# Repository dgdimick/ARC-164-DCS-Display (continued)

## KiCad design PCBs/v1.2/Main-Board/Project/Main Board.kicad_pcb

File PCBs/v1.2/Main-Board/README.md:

# ARC-164 Main Board — Version 1.2

**Last updated: November 10, 2026 at 6:08 PM MST (America/Denver)**

**LED Sub Board v1.2 is now published for Main Board v1.2.** I printed the latest mockup at **100%** and it passed the fit test, including **frequency and channel LED alignment and J20 connector/cable clearance**. The final layout keeps the **FREQ LEDs up 0.5 mm**, the **channel LEDs up 0.5 mm with their earlier 0.5 mm leftward adjustment**, and **J20 up 2 mm total** from the previous mounting position. The **0.75 mm gaps, 6 mm display bodies and tested 8 mm mounting stack** remain unchanged. **Use Main Board v1.2 with LED Sub Board v1.2; older Sub Boards do not match this Main Board. Assembled electrical testing is still pending.**

## Downloads

- [Complete Main Board v1.2 package](Main-Board-v1.2.zip)
- [KiCad project](Project/Main%20Board.kicad_pro)
- [Schematic PDF](Schematics/Main-Board-v1.2.pdf)
- [Component BOM](Assembly/BOM.csv)
- [Gerber and drill ZIP](Main-Board-v1.2-Gerbers.zip)
- [Main Board print mockup — 100% scale](STLs/ARC-164_Main_Board_v1.2_100pct.stl)
- [DRC and schematic parity report](Checks/DRC.rpt) · [ERC report](Checks/ERC.rpt)

I’ve resized this Main Board and moved the Sub Board mounting holes to match the new layout. The silkscreen and PCB/schematic revision fields identify **v1.2**. This release contains only the Main Board; it does not include the unfinished matching Sub Board.

I moved **J10 to my chosen position**, aligned **SW12 (LOAD/reed) and SW13 (TEST DISPLAY)** below R4, and updated the routing and ground fills. Their matching solder pads now line up horizontally. All other component positions, the outline and mounting holes are unchanged from my latest saved layout.

Fresh KiCad checks report **zero DRC violations, zero unconnected items, zero schematic parity issues and zero ERC violations under the saved project settings**. Disabled checks are listed in the reports. These checks do not prove physical cable clearance or assembled electrical operation. The two 40-pin interfaces use cables, not direct stacking connectors.

## Mounting and compatibility

**Use Main Board v1.2 with the matching LED Sub Board v1.2.** The latest Sub Board mockup passed my **100% print and fit test on November 10, 2026**, including LED alignment and J20 connector/cable clearance. Older Sub Boards do not match Main Board v1.2. Assembled electrical testing remains pending. [Sub Board v1.2 downloads](../LED-Subboard/README.md).

The previously tested Sub Board mounting stack is **8 mm**: each of four mounts uses a **20 mm screw, 6 mm-thick nut and two 1 mm washers**. Panel-to-Main-Board spacing is currently **13.5 mm**; I may use **14 mm** to recess the displays slightly from the glass, subject to the real PCB fit. The Power Driver Board remains at v1.0 Prototype and mounts below Main, components facing down, on **10 standoffs longer than 20 mm**.

[Assembly notes](../../v1.0-Prototype/Docs/Assembly.md) · [Wiring and pinouts](../../v1.0-Prototype/Docs/Wiring.md)

## MAIN and PRESET wiring

I wire each MAIN (SW7) and PRESET (SW8) contact directly to its own Teensy GPIO input through J10.
Both switch commons connect to ground. The selected contact pulls its input low when the Teensy
internal pull-up is enabled. This circuit uses no resistor ladders.

| Switch contact | J10 pin on both boards | Teensy GPIO |
| --- | ---: | ---: |
| MAIN position 1 | 20 | 18 |
| MAIN position 2 | 21 | 19 |
| MAIN position 3 | 22 | 20 |
| MAIN position 4 | 23 | 21 |
| PRESET position 1 | 24 | 22 |
| PRESET position 2 | 25 | 23 |
| PRESET position 3 | 26 | 24 |

The GPIO column uses the pin numbers printed on the Teensy. Assembled electrical testing is still pending.

## Version history

- **1.2 — November 9, 2026:** New J10 position, aligned SW12/SW13 solder pads, updated routing and ground fills, and v1.2 PCB/schematic revision markings. The matching Sub Board was not yet published at this release; it was published as v1.2 on November 10 after the physical fit test. Assembled electrical testing remains pending.
- [1.1 — November 9, 2026](../../v1.1/Main-Board/README.md): Resized Main Board and updated mounting holes; superseded by v1.2.
- **1.0 Prototype — November 7, 2026:** Initial publication, subsequently withdrawn.

[PCB overview](../../README.md)

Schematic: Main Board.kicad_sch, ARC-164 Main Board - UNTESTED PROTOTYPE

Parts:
D1, D2, D3, D4, D5, D6, D7, D8, D9, D10, D11, D12, D13, D14, D15, D16, D17, D18, D19: WP710A10SGD; LED_D3.0mm_Green
J10: Controls cable to Power Driver Board J10; PinHeader_2x20_P2.54mm_Vertical
J21: Backlight power from driver J21; PinHeader_1x03_P2.54mm_Vertical
J22: Auxiliary resistor-limited backlight output; WireSolderPads_1x02_P4.6mm_D1.7mm_18AWG
R1, R2, R3, R4, R5, R6, R7, R8, R9, R10, R11, R12, R13, R14, R15, R16, R17, R18, R19: 330; R_Axial_DIN0207_L6.3mm_D2.5mm_P10.16mm_Horizontal
SW1, SW2, SW3, SW4, SW5, SW6, SW9: PEC11R-4230F-S0024; PEC11R4230FS0024
SW7, SW8: A12505RNCQ
SW10: TONE - wire solder pads; WireSolderPads_1x02_P4.6mm_D1.7mm_18AWG
SW11: SQL - wire solder pads; WireSolderPads_1x02_P4.6mm_D1.7mm_18AWG
SW12: LOAD (magnetic reed) - wire solder pads; WireSolderPads_1x02_P4.6mm_D1.7mm_18AWG
SW13: TEST_DISPLAY - wire solder pads; WireSolderPads_1x02_P4.6mm_D1.7mm_18AWG
SW14: STATUS - wire solder pads; WireSolderPads_1x02_P4.6mm_D1.7mm_18AWG

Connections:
/BACKLIGHT_RETURN: D1.1 (K), D2.1 (K), D3.1 (K), D4.1 (K), D5.1 (K), D6.1 (K), D7.1 (K), D8.1 (K), D9.1 (K), D10.1 (K), D11.1 (K), D12.1 (K), D13.1 (K), D14.1 (K), D15.1 (K), D16.1 (K), D17.1 (K), D18.1 (K), D19.1 (K), J21.2, J22.2
/BL_ANODE_01: D1.2 (A), R1.2
/BL_ANODE_02: D2.2 (A), R2.2
/BL_ANODE_03: D3.2 (A), R3.2
/BL_ANODE_05: D4.2 (A), R4.2
/BL_ANODE_06: D5.2 (A), R5.2
/BL_ANODE_07: D6.2 (A), R6.2
/BL_ANODE_09: D7.2 (A), R7.2
/BL_ANODE_10: D8.2 (A), R8.2
/BL_ANODE_11: D9.2 (A), R9.2
/BL_ANODE_13: D10.2 (A), R10.2
/BL_ANODE_14: D11.2 (A), R11.2
/BL_ANODE_15: D12.2 (A), R12.2
/BL_ANODE_17: D13.2 (A), R13.2
/BL_ANODE_18: D14.2 (A), R14.2
/BL_ANODE_19: D15.2 (A), R15.2
/BL_ANODE_21: D16.2 (A), R16.2
/BL_ANODE_22: D17.2 (A), R17.2
/BL_ANODE_23: D18.2 (A), R18.2
/BL_ANODE_25: D19.2 (A), R19.2
/CHANNEL_A: J10.16, SW6.A
/CHANNEL_B: J10.17, SW6.B
/FREQ1_A: J10.6, SW1.A
/FREQ1_B: J10.7, SW1.B
/FREQ2_A: J10.8, SW2.A
/FREQ2_B: J10.9, SW2.B
/FREQ3_A: J10.10, SW3.A
/FREQ3_B: J10.11, SW3.B
/FREQ4_A: J10.12, SW4.A
/FREQ4_B: J10.13, SW4.B
/FREQ5_A: J10.14, SW5.A
/FREQ5_B: J10.15, SW5.B
/GND: J10.1, J10.32, J21.3, SW1.C, SW1.MH1 (CASE), SW1.MH2 (CASE), SW2.C, SW2.MH1 (CASE), SW2.MH2 (CASE), SW3.C, SW3.MH1 (CASE), SW3.MH2 (CASE), SW4.C, SW4.MH1 (CASE), SW4.MH2 (CASE), SW5.C, SW5.MH1 (CASE), SW5.MH2 (CASE), SW6.C, SW6.MH1 (CASE), SW6.MH2 (CASE), SW7.A1 (COM), SW8.A1 (COM), SW9.C, SW9.MH1 (CASE), SW9.MH2 (CASE), SW10.2 (B), SW11.2 (B), SW12.2, SW13.2, SW14.2
/LED_5V: J21.1, J22.1, R1.1, R2.1, R3.1, R4.1, R5.1, R6.1, R7.1, R8.1, R9.1, R10.1, R11.1, R12.1, R13.1, R14.1, R15.1, R16.1, R17.1, R18.1, R19.1
/LOAD: J10.29, SW12.1
/MAIN_POS1: J10.20, SW7.1
/MAIN_POS2: J10.21, SW7.2
/MAIN_POS3: J10.22, SW7.4 (3)
/MAIN_POS4: J10.23, SW7.5 (4)
/PRESET_POS1: J10.24, SW8.1
/PRESET_POS2: J10.25, SW8.2
/PRESET_POS3: J10.26, SW8.4 (3)
/SQL: J10.28, SW11.1 (A)
/STATUS: J10.31, SW14.1
/TEST_DISPLAY: J10.30, SW13.1
/TONE: J10.27, SW10.1 (A)
/VOL_A: J10.18, SW9.A
/VOL_B: J10.19, SW9.B

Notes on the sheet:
ARC-164 Main Board: panel controls and backlight LEDs
J10 control cable mates pin-for-pin to driver J10. Pins 2-5 and 33-40 reserved NC. Inputs use Teensy 3.3V pull-ups.
J21: 1 regulated LED 5V; 2 MOSFET-switched LED return; 3 common ground. Never connect return pin 2 directly to GND.
19 green backlight LEDs are panel-facing on Main Board. Each has an individual 330 ohm series resistor; test physical fit and brightness.
19 provisional green backlight LEDs, each with 330 ohm series resistor. Driver PCB supplies DCS-BIOS PWM dimming.
BACKLIGHT: 19 provisional green LED branches. Position under lettering; count may change.
Each branch: LED_5V -> 330 ohm resistor -> LED anode; cathode -> BACKLIGHT_RETURN (PWM switched, not GND).

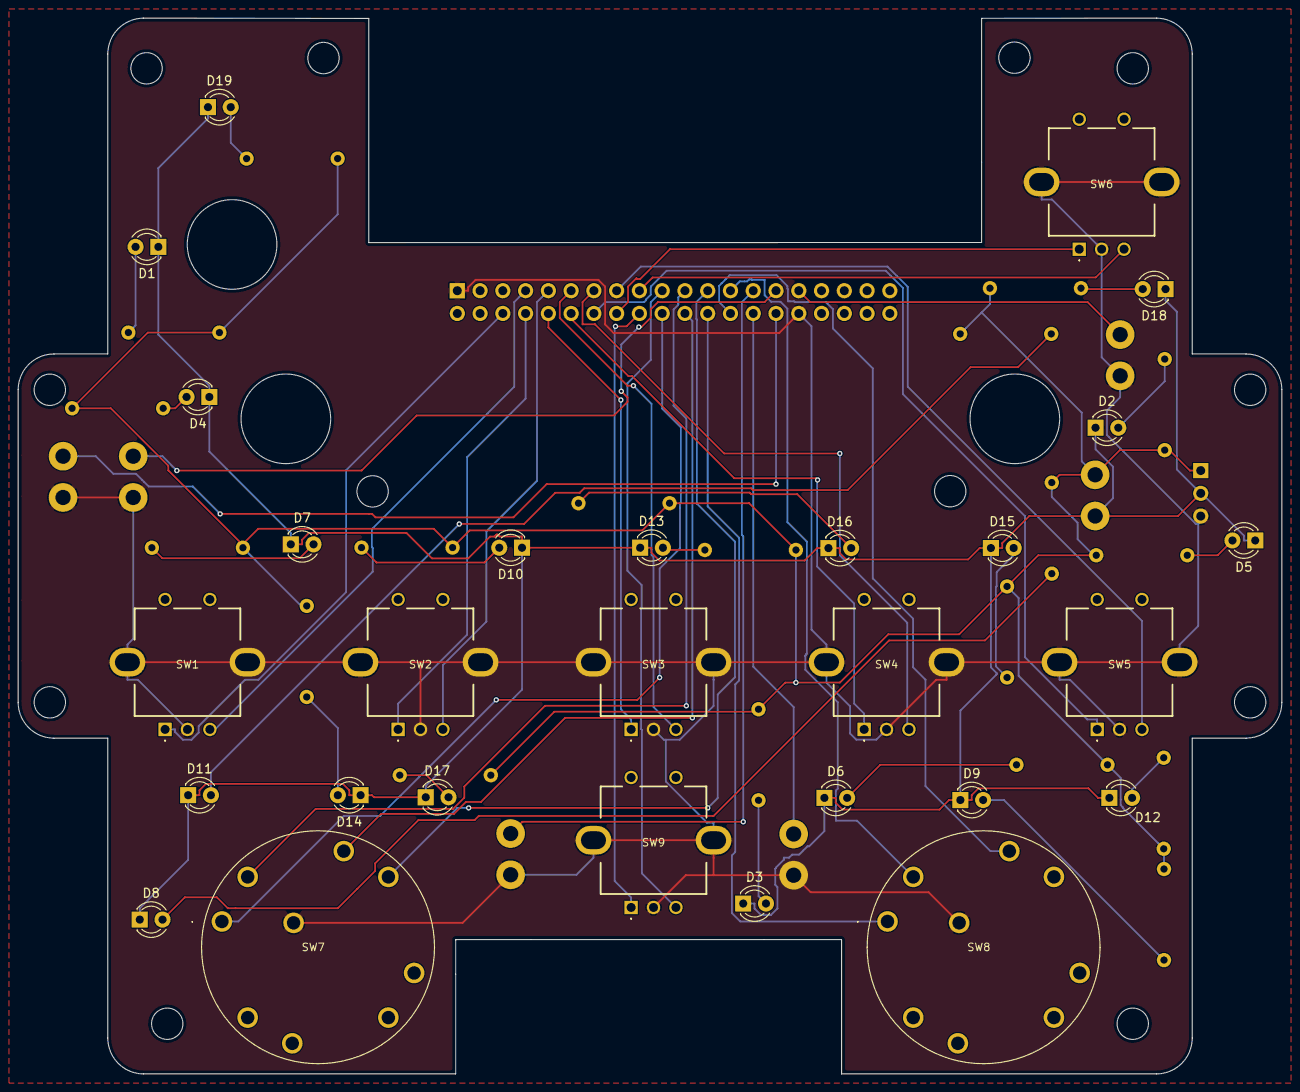
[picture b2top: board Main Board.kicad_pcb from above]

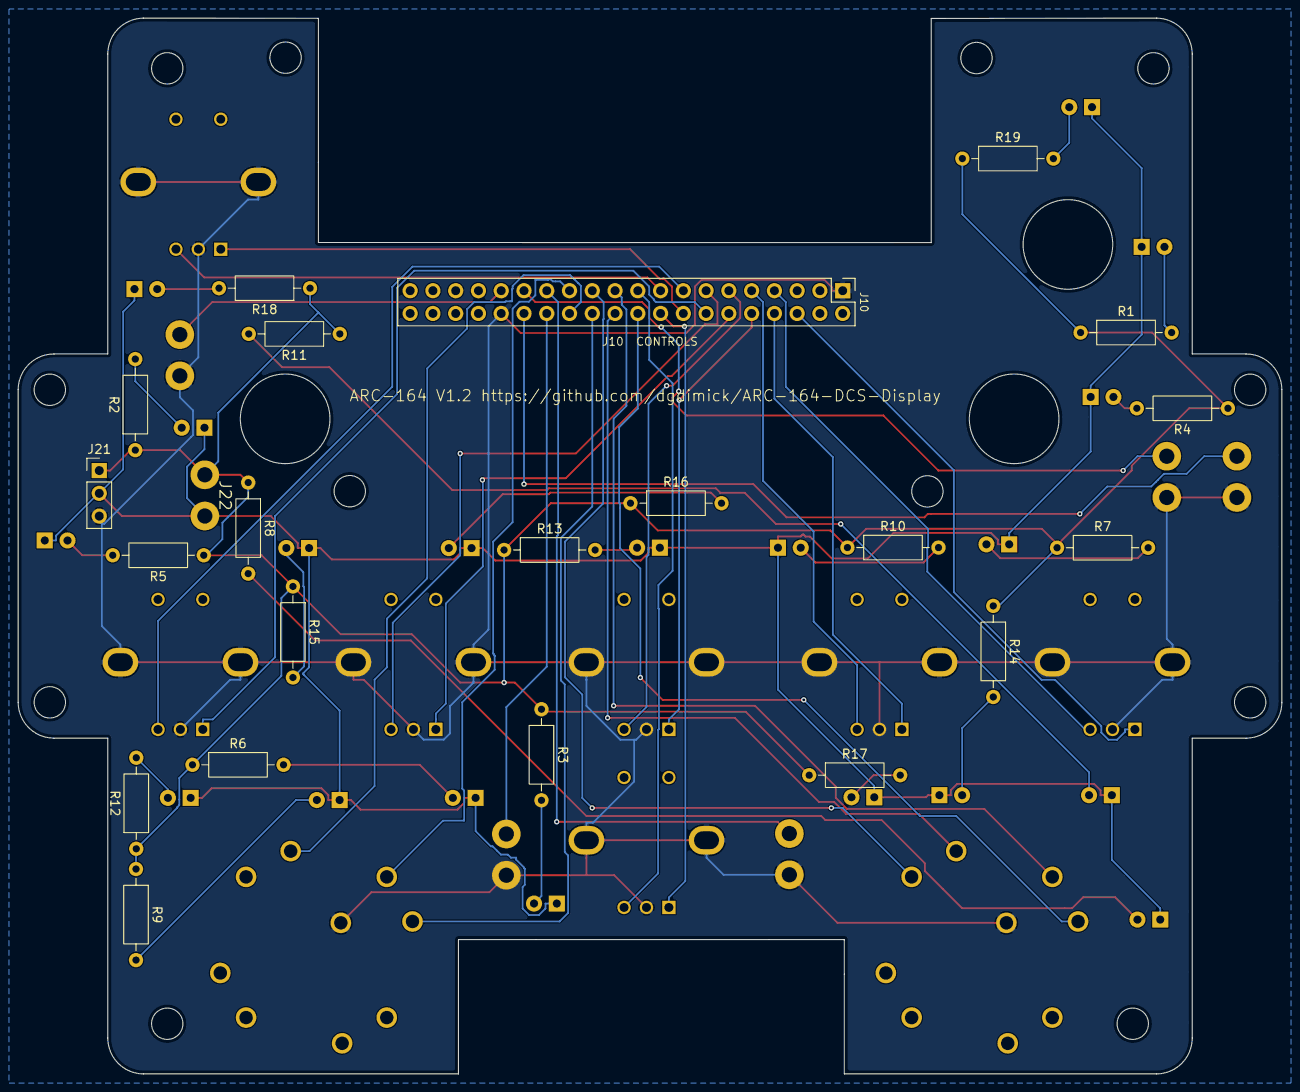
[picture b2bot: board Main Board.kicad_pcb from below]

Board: 2 copper layers, 141.0 x 117.8 mm, 55 parts (27 on the bottom side), 48 nets.

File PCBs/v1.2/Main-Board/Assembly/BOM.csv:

"Refs","Value","Footprint","Qty","DNP"
"D1","WP710A10SGD","ARC164_Backlight:LED_D3.0mm_Green","1",""
"D2","WP710A10SGD","ARC164_Backlight:LED_D3.0mm_Green","1",""
"D3","WP710A10SGD","ARC164_Backlight:LED_D3.0mm_Green","1",""
"D4","WP710A10SGD","ARC164_Backlight:LED_D3.0mm_Green","1",""
"D5","WP710A10SGD","ARC164_Backlight:LED_D3.0mm_Green","1",""
"D6","WP710A10SGD","ARC164_Backlight:LED_D3.0mm_Green","1",""
"D7","WP710A10SGD","ARC164_Backlight:LED_D3.0mm_Green","1",""
"D8","WP710A10SGD","ARC164_Backlight:LED_D3.0mm_Green","1",""
"D9","WP710A10SGD","ARC164_Backlight:LED_D3.0mm_Green","1",""
"D10","WP710A10SGD","ARC164_Backlight:LED_D3.0mm_Green","1",""
"D11","WP710A10SGD","ARC164_Backlight:LED_D3.0mm_Green","1",""
"D12","WP710A10SGD","ARC164_Backlight:LED_D3.0mm_Green","1",""
"D13","WP710A10SGD","ARC164_Backlight:LED_D3.0mm_Green","1",""
"D14","WP710A10SGD","ARC164_Backlight:LED_D3.0mm_Green","1",""
"D15","WP710A10SGD","ARC164_Backlight:LED_D3.0mm_Green","1",""
"D16","WP710A10SGD","ARC164_Backlight:LED_D3.0mm_Green","1",""
"D17","WP710A10SGD","ARC164_Backlight:LED_D3.0mm_Green","1",""
"D18","WP710A10SGD","ARC164_Backlight:LED_D3.0mm_Green","1",""
"D19","WP710A10SGD","ARC164_Backlight:LED_D3.0mm_Green","1",""
"J10","Controls cable to Power Driver Board J10","Connector_PinHeader_2.54mm:PinHeader_2x20_P2.54mm_Vertical","1",""
"J21","Backlight power from driver J21","Connector_PinHeader_2.54mm:PinHeader_1x03_P2.54mm_Vertical","1",""
"J22","Auxiliary resistor-limited backlight output","ARC164_WirePads:WireSolderPads_1x02_P4.6mm_D1.7mm_18AWG","1",""
"R1","330","Resistor_THT:R_Axial_DIN0207_L6.3mm_D2.5mm_P10.16mm_Horizontal","1",""
"R2","330","Resistor_THT:R_Axial_DIN0207_L6.3mm_D2.5mm_P10.16mm_Horizontal","1",""
"R3","330","Resistor_THT:R_Axial_DIN0207_L6.3mm_D2.5mm_P10.16mm_Horizontal","1",""
"R4","330","Resistor_THT:R_Axial_DIN0207_L6.3mm_D2.5mm_P10.16mm_Horizontal","1",""
"R5","330","Resistor_THT:R_Axial_DIN0207_L6.3mm_D2.5mm_P10.16mm_Horizontal","1",""
"R6","330","Resistor_THT:R_Axial_DIN0207_L6.3mm_D2.5mm_P10.16mm_Horizontal","1",""
"R7","330","Resistor_THT:R_Axial_DIN0207_L6.3mm_D2.5mm_P10.16mm_Horizontal","1",""
"R8","330","Resistor_THT:R_Axial_DIN0207_L6.3mm_D2.5mm_P10.16mm_Horizontal","1",""
"R9","330","Resistor_THT:R_Axial_DIN0207_L6.3mm_D2.5mm_P10.16mm_Horizontal","1",""
"R10","330","Resistor_THT:R_Axial_DIN0207_L6.3mm_D2.5mm_P10.16mm_Horizontal","1",""
"R11","330","Resistor_THT:R_Axial_DIN0207_L6.3mm_D2.5mm_P10.16mm_Horizontal","1",""
"R12","330","Resistor_THT:R_Axial_DIN0207_L6.3mm_D2.5mm_P10.16mm_Horizontal","1",""
"R13","330","Resistor_THT:R_Axial_DIN0207_L6.3mm_D2.5mm_P10.16mm_Horizontal","1",""
"R14","330","Resistor_THT:R_Axial_DIN0207_L6.3mm_D2.5mm_P10.16mm_Horizontal","1",""
"R15","330","Resistor_THT:R_Axial_DIN0207_L6.3mm_D2.5mm_P10.16mm_Horizontal","1",""
"R16","330","Resistor_THT:R_Axial_DIN0207_L6.3mm_D2.5mm_P10.16mm_Horizontal","1",""
"R17","330","Resistor_THT:R_Axial_DIN0207_L6.3mm_D2.5mm_P10.16mm_Horizontal","1",""
"R18","330","Resistor_THT:R_Axial_DIN0207_L6.3mm_D2.5mm_P10.16mm_Horizontal","1",""
"R19","330","Resistor_THT:R_Axial_DIN0207_L6.3mm_D2.5mm_P10.16mm_Horizontal","1",""
"SW1","PEC11R-4230F-S0024","ARC210_Encoders:PEC11R4230FS0024","1",""
"SW2","PEC11R-4230F-S0024","ARC210_Encoders:PEC11R4230FS0024","1",""
"SW3","PEC11R-4230F-S0024","ARC210_Encoders:PEC11R4230FS0024","1",""
"SW4","PEC11R-4230F-S0024","ARC210_Encoders:PEC11R4230FS0024","1",""
"SW5","PEC11R-4230F-S0024","ARC210_Encoders:PEC11R4230FS0024","1",""
"SW6","PEC11R-4230F-S0024","ARC210_Encoders:PEC11R4230FS0024","1",""
"SW7","A12505RNCQ","ARC164_Switches:A12505RNCQ","1",""
"SW8","A12505RNCQ","ARC164_Switches:A12505RNCQ","1",""
"SW9","PEC11R-4230F-S0024","ARC210_Encoders:PEC11R4230FS0024","1",""
"SW10","TONE - wire solder pads","ARC164_WirePads:WireSolderPads_1x02_P4.6mm_D1.7mm_18AWG","1",""
"SW11","SQL - wire solder pads","ARC164_WirePads:WireSolderPads_1x02_P4.6mm_D1.7mm_18AWG","1",""
"SW12","LOAD (magnetic reed) - wire solder pads","ARC164_WirePads:WireSolderPads_1x02_P4.6mm_D1.7mm_18AWG","1",""
"SW13","TEST_DISPLAY - wire solder pads","ARC164_WirePads:WireSolderPads_1x02_P4.6mm_D1.7mm_18AWG","1",""
"SW14","STATUS - wire solder pads","ARC164_WirePads:WireSolderPads_1x02_P4.6mm_D1.7mm_18AWG","1",""
